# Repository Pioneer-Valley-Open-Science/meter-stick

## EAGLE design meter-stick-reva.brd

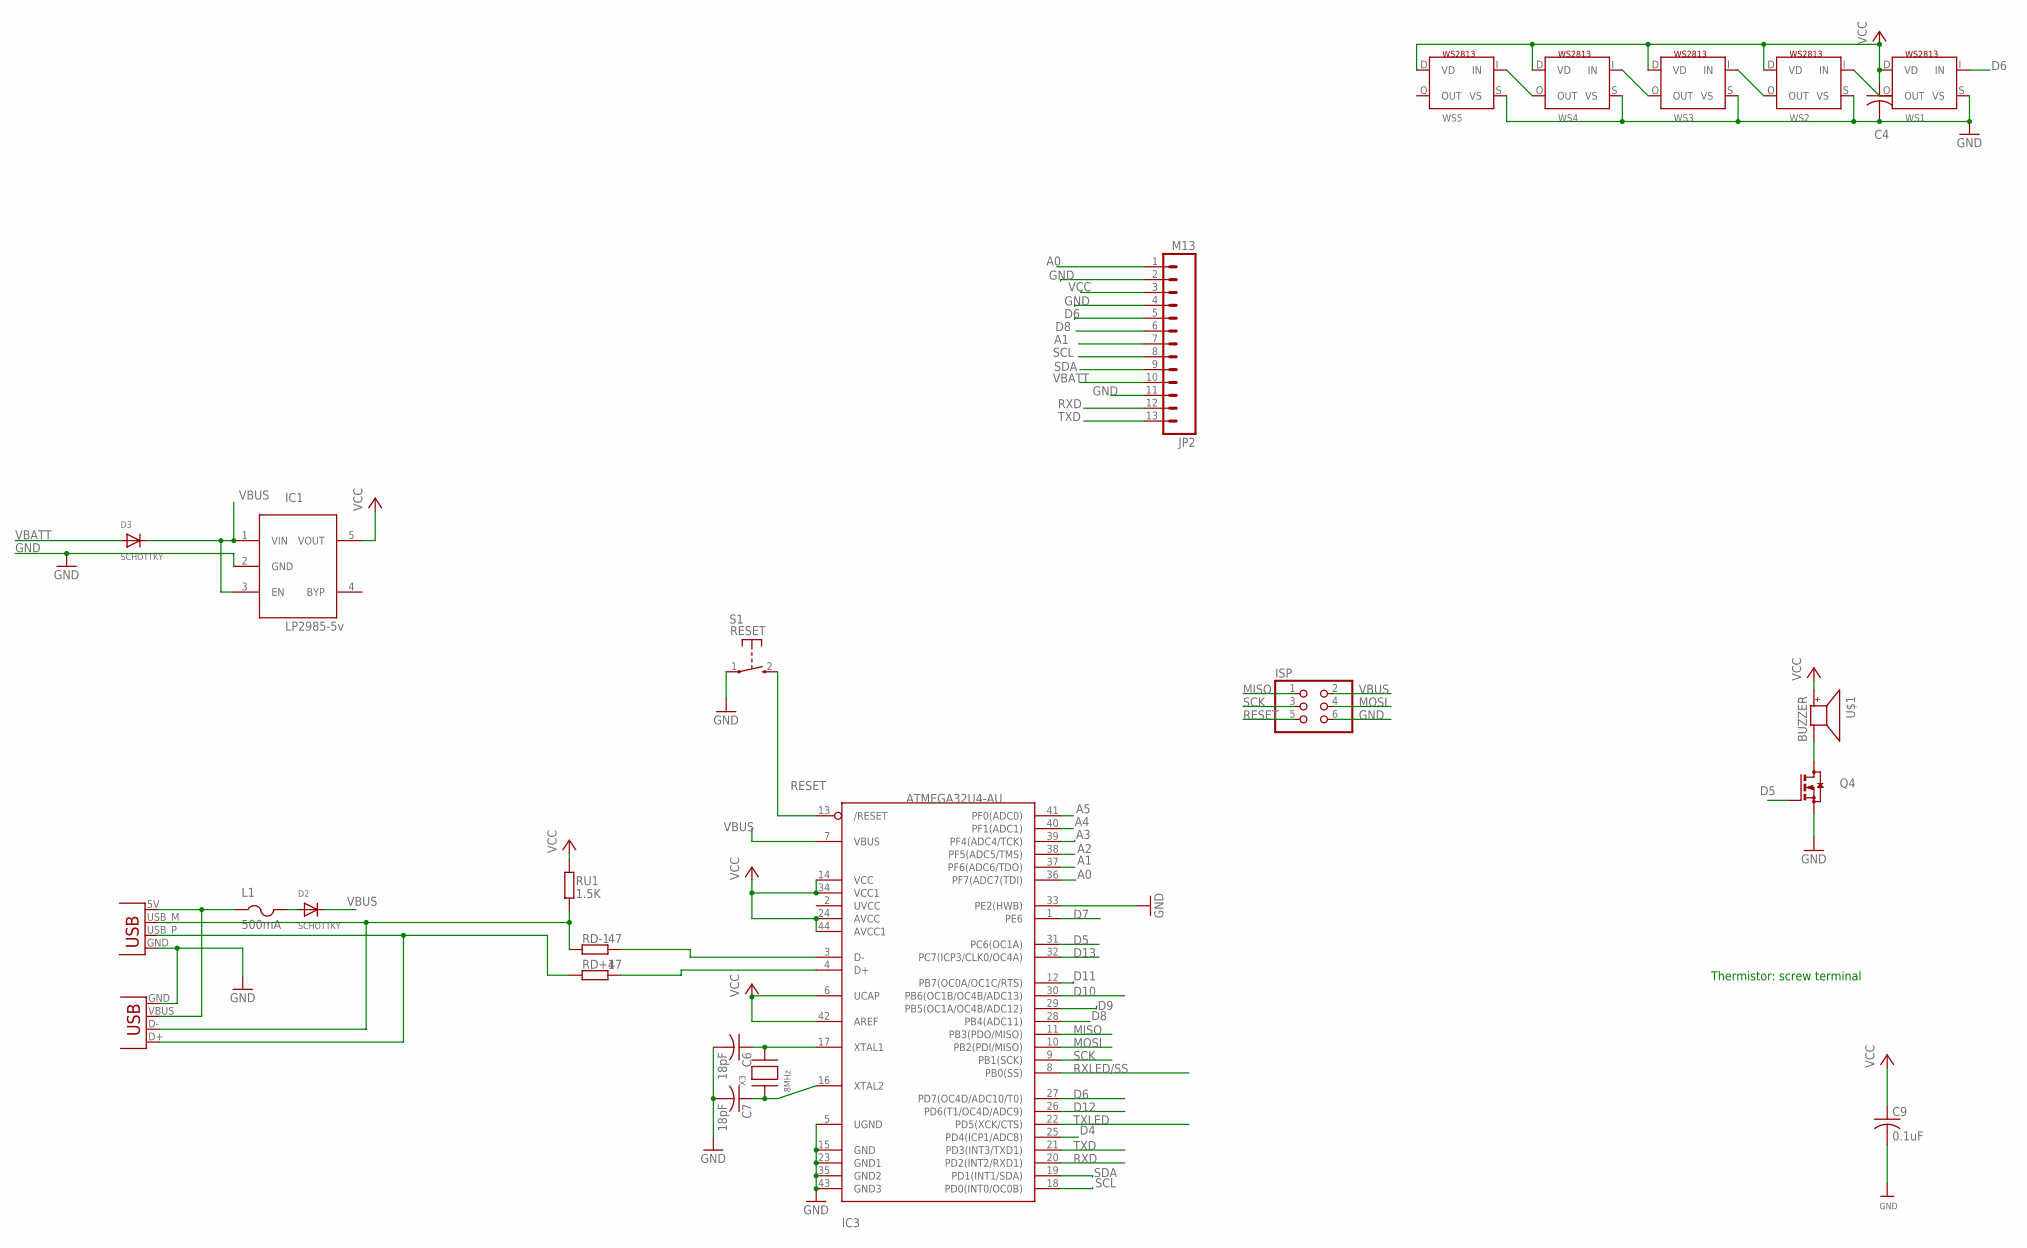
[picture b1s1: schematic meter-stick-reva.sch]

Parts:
C4: C-USC0805K; C0805K
C6, C7: 18pF; C0805K
C9: 0.1uF; C0805
D2, D3: SCHOTTKY; SOD-123
IC1: LP2985-5v; SOT23-5L
IC3: ATMEGA32U4-AU; TQFP44
ISP: PINHD-2X3; 2X03
JP2: M13; 1X13
L1: 500mA; R1206
P1: USBPCB; USB-A-PCB
Q4: BSS123; SOT23
RD+1: 47; R0805
RD-1: 47; R0805
RU1: 1.5K; R0805
S1: RESET; TACTILE_SWITCH_SMD_2PIN_TINY
U$1: BUZZER; SMT-8585-BUZZER
WS1, WS2, WS3, WS4, WS5: WS2813; RGBLED5050_4
X2: USBSMD; USB-MINIB
X3: 8MHz; NX5032

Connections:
A0: IC3.36 (PF7(ADC7(TDI)), JP2.1
A1: IC3.37 (PF6(ADC6/TDO)), JP2.7
A2: IC3.38 (PF5(ADC5/TMS))
A3: IC3.39 (PF4(ADC4/TCK))
A4: IC3.40 (PF1(ADC1))
A5: IC3.41 (PF0(ADC0))
D4: IC3.25 (PD4(ICP1/ADC8))
D5: IC3.31 (PC6(OC1A)), Q4.1 (G)
D6: IC3.27 (PD7(OC4D/ADC10/T0)), JP2.5, WS1.I (IN)
D7: IC3.1 (PE6)
D8: IC3.28 (PB4(ADC11)), JP2.6
D9: IC3.29 (PB5(OC1A/OC4B/ADC12))
D10: IC3.30 (PB6(OC1B/OC4B/ADC13))
D11: IC3.12 (PB7(OC0A/OC1C/RTS))
D12: IC3.26 (PD6(T1/OC4D/ADC9))
D13: IC3.32 (PC7(ICP3/CLK0/OC4A))
D-: P1.USB_M (D-), RD-1.1, RU1.1, X2.D-
GND: C4.2, C6.2, C7.2, C9.2, IC1.2 (GND), IC3.5 (UGND), IC3.15 (GND), IC3.23 (GND1), IC3.33 (PE2(HWB)), IC3.35 (GND2), IC3.43 (GND3), ISP.6, JP2.2, JP2.4, JP2.11, P1.GND, Q4.2 (S), S1.1, WS1.S (VS), WS2.S (VS), WS3.S (VS), WS4.S (VS), WS5.S (VS), X2.GND
MISO: IC3.11 (PB3(PDO/MISO)), ISP.1
MOSI: IC3.10 (PB2(PDI/MISO)), ISP.4
unnamed: D2.A, L1.2
unnamed: C7.1, IC3.16 (XTAL2), X3.P$1
unnamed: C6.1, IC3.17 (XTAL1), X3.P$2
unnamed: P1.USB_P (D+), RD+1.1, X2.D+
unnamed: Q4.3 (D), U$1.-
unnamed: WS4.O (OUT), WS5.I (IN)
unnamed: IC3.4 (D+), RD+1.2
unnamed: IC3.3 (D-), RD-1.2
unnamed: WS1.O (OUT), WS2.I (IN)
unnamed: WS2.O (OUT), WS3.I (IN)
unnamed: WS3.O (OUT), WS4.I (IN)
RESET: IC3.13 (/RESET), ISP.5, S1.2 (S)
RXD: IC3.20 (PD2(INT2/RXD1)), JP2.12
RXLED/SS: IC3.8 (PB0(SS))
SCK: IC3.9 (PB1(SCK)), ISP.3
SCL: IC3.18 (PD0(INT0/OC0B)), JP2.8
SDA: IC3.19 (PD1(INT1/SDA)), JP2.9
TXD: IC3.21 (PD3(INT3/TXD1)), JP2.13
TXLED: IC3.22 (PD5(XCK/CTS))
VBATT: D3.A, JP2.10
VBUS: D2.C, D3.C, IC1.1 (VIN), IC1.3 (EN), IC3.7 (VBUS), ISP.2
VBUS1: L1.1, P1.5V (VBUS), X2.VBUS
VCC: C4.1, C9.1, IC1.5 (VOUT), IC3.6 (UCAP), IC3.14 (VCC), IC3.24 (AVCC), IC3.34 (VCC1), IC3.42 (AREF), IC3.44 (AVCC1), JP2.3, RU1.2, U$1.+, WS1.D (VD), WS2.D (VD), WS3.D (VD), WS4.D (VD), WS5.D (VD)

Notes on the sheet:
Thermistor: screw terminal

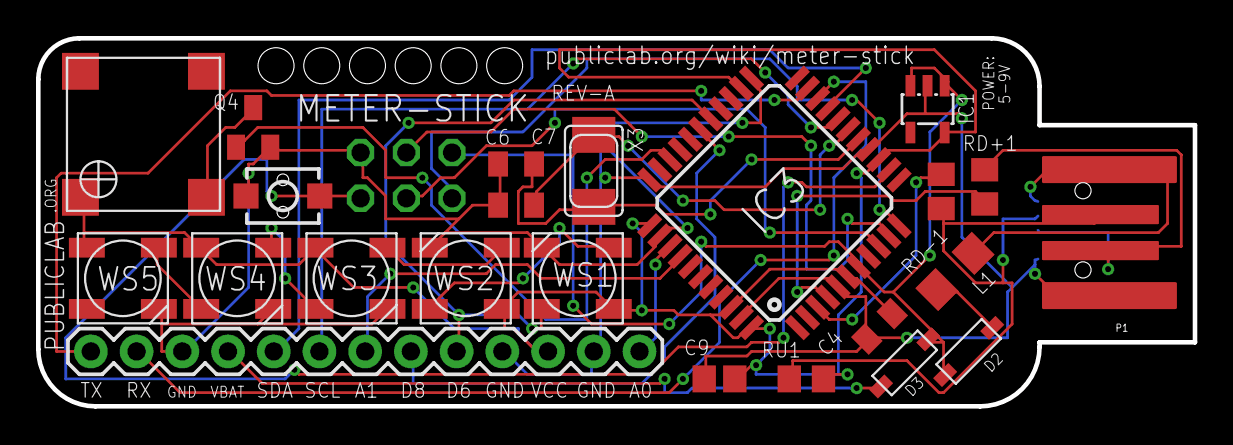
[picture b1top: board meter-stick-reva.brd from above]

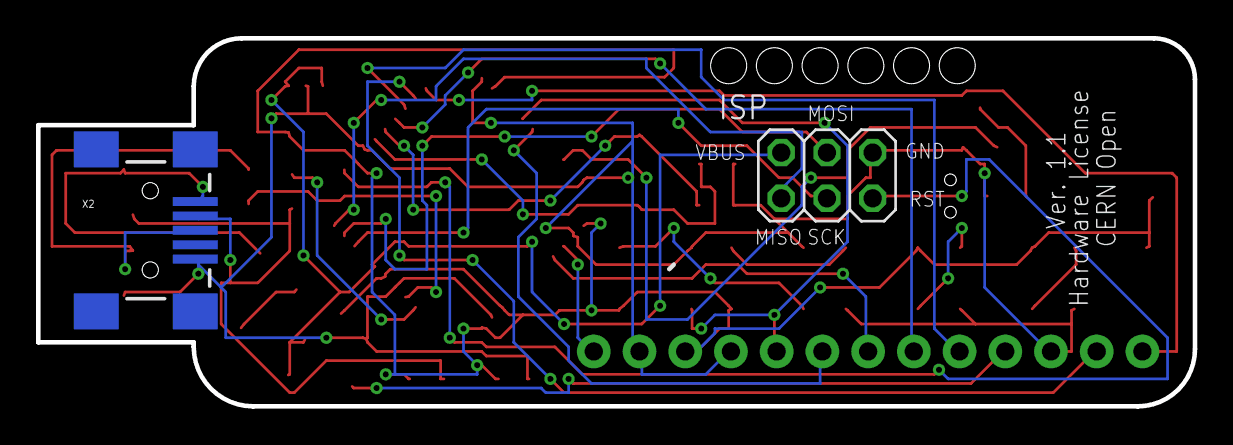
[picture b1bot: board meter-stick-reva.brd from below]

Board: 2 copper layers, 64.3 x 20.4 mm, 25 parts (2 on the bottom side), 30 nets.

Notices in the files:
meter-stick-reva.brd:
Hardware License
parts and their libraries:
SparkFun-Connectors: Licensing: Creative Commons ShareAlike 4.0 International - https://creativecommons.org/licenses/by-sa/4.0
microbuilder: This work is placed in the public domain, and may be freely used for commercial and non-commercial work with the following conditions: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
